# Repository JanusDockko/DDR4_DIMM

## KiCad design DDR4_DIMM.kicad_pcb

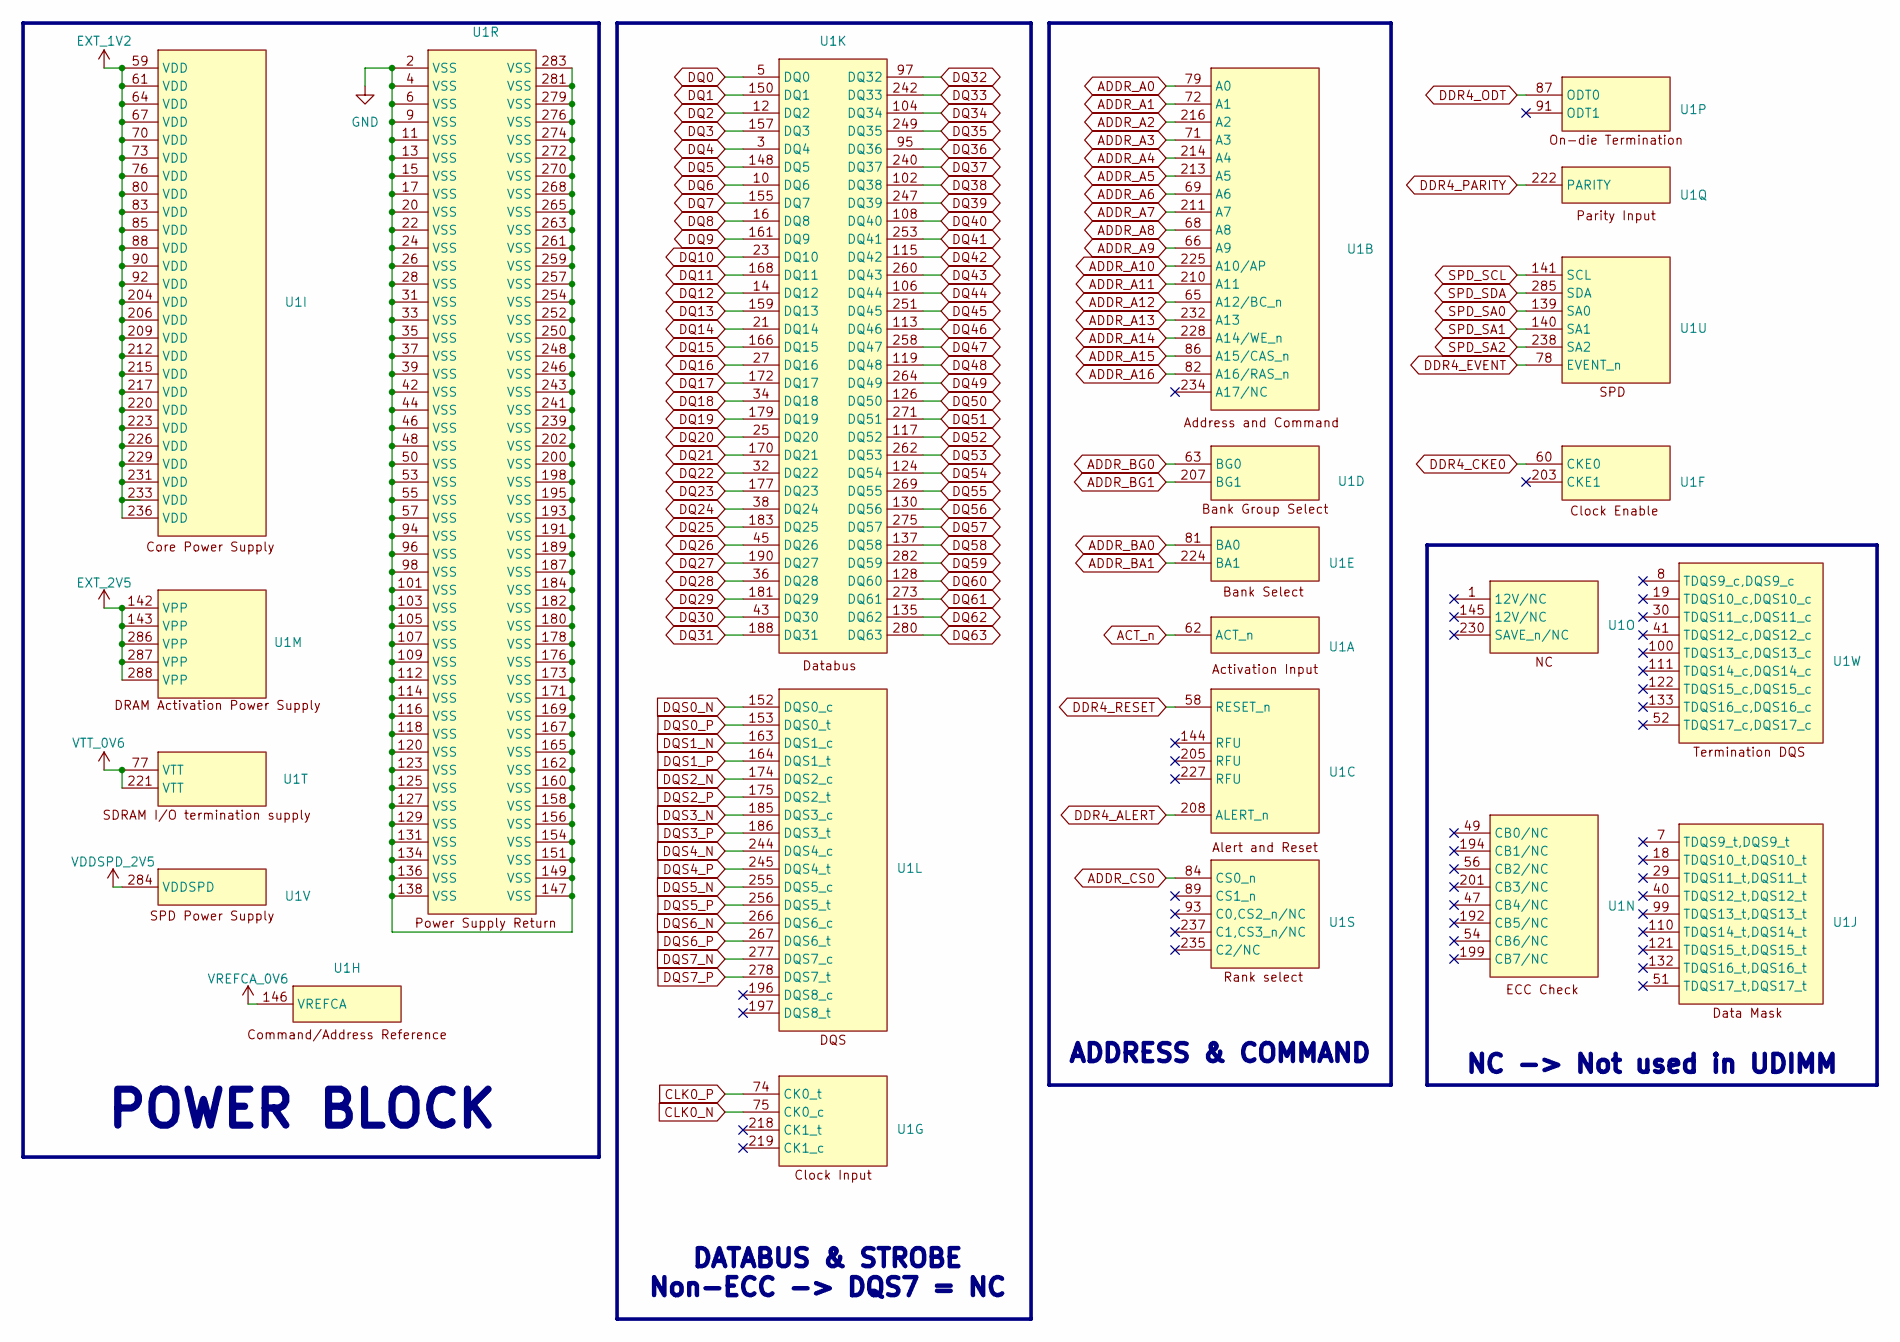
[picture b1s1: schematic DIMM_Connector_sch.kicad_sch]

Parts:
U1: DIMM_Connector_288Pin

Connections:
ACT_n: U1.62 (ACT_n); also elsewhere on the board
ADDR_A0: U1.79 (A0); also elsewhere on the board
ADDR_A1: U1.72 (A1); also elsewhere on the board
ADDR_A2: U1.216 (A2); also elsewhere on the board
ADDR_A3: U1.71 (A3); also elsewhere on the board
ADDR_A4: U1.214 (A4); also elsewhere on the board
ADDR_A5: U1.213 (A5); also elsewhere on the board
ADDR_A6: U1.69 (A6); also elsewhere on the board
ADDR_A7: U1.211 (A7); also elsewhere on the board
ADDR_A8: U1.68 (A8); also elsewhere on the board
ADDR_A9: U1.66 (A9); also elsewhere on the board
ADDR_A10: U1.225 (A10/AP); also elsewhere on the board
ADDR_A11: U1.210 (A11); also elsewhere on the board
ADDR_A12: U1.65 (A12/BC_n); also elsewhere on the board
ADDR_A13: U1.232 (A13); also elsewhere on the board
ADDR_A14: U1.228 (A14/WE_n); also elsewhere on the board
ADDR_A15: U1.86 (A15/CAS_n); also elsewhere on the board
ADDR_A16: U1.82 (A16/RAS_n); also elsewhere on the board
ADDR_BA0: U1.81 (BA0); also elsewhere on the board
ADDR_BA1: U1.224 (BA1); also elsewhere on the board
ADDR_BG0: U1.63 (BG0); also elsewhere on the board
ADDR_BG1: U1.207 (BG1); also elsewhere on the board
ADDR_CS0: U1.84 (CS0_n); also elsewhere on the board
CLK0_N: U1.75 (CK0_c); also elsewhere on the board
CLK0_P: U1.74 (CK0_t); also elsewhere on the board
DDR4_ALERT: U1.208 (ALERT_n); also elsewhere on the board
DDR4_CKE0: U1.60 (CKE0); also elsewhere on the board
DDR4_EVENT: U1.78 (EVENT_n); also elsewhere on the board
DDR4_ODT: U1.87 (ODT0); also elsewhere on the board
DDR4_PARITY: U1.222 (PARITY); also elsewhere on the board
DDR4_RESET: U1.58 (RESET_n); also elsewhere on the board
DQ0: U1.5 (DQ0); also elsewhere on the board
DQ1: U1.150 (DQ1); also elsewhere on the board
DQ2: U1.12 (DQ2); also elsewhere on the board
DQ3: U1.157 (DQ3); also elsewhere on the board
DQ4: U1.3 (DQ4); also elsewhere on the board
DQ5: U1.148 (DQ5); also elsewhere on the board
DQ6: U1.10 (DQ6); also elsewhere on the board
DQ7: U1.155 (DQ7); also elsewhere on the board
DQ8: U1.16 (DQ8); also elsewhere on the board
DQ9: U1.161 (DQ9); also elsewhere on the board
DQ10: U1.23 (DQ10); also elsewhere on the board
DQ11: U1.168 (DQ11); also elsewhere on the board
DQ12: U1.14 (DQ12); also elsewhere on the board
DQ13: U1.159 (DQ13); also elsewhere on the board
DQ14: U1.21 (DQ14); also elsewhere on the board
DQ15: U1.166 (DQ15); also elsewhere on the board
DQ16: U1.27 (DQ16); also elsewhere on the board
DQ17: U1.172 (DQ17); also elsewhere on the board
DQ18: U1.34 (DQ18); also elsewhere on the board
DQ19: U1.179 (DQ19); also elsewhere on the board
DQ20: U1.25 (DQ20); also elsewhere on the board
DQ21: U1.170 (DQ21); also elsewhere on the board
DQ22: U1.32 (DQ22); also elsewhere on the board
DQ23: U1.177 (DQ23); also elsewhere on the board
DQ24: U1.38 (DQ24); also elsewhere on the board
DQ25: U1.183 (DQ25); also elsewhere on the board
DQ26: U1.45 (DQ26); also elsewhere on the board
DQ27: U1.190 (DQ27); also elsewhere on the board
DQ28: U1.36 (DQ28); also elsewhere on the board
DQ29: U1.181 (DQ29); also elsewhere on the board
DQ30: U1.43 (DQ30); also elsewhere on the board
DQ31: U1.188 (DQ31); also elsewhere on the board
DQ32: U1.97 (DQ32); also elsewhere on the board
DQ33: U1.242 (DQ33); also elsewhere on the board
DQ34: U1.104 (DQ34); also elsewhere on the board
DQ35: U1.249 (DQ35); also elsewhere on the board
DQ36: U1.95 (DQ36); also elsewhere on the board
DQ37: U1.240 (DQ37); also elsewhere on the board
DQ38: U1.102 (DQ38); also elsewhere on the board
DQ39: U1.247 (DQ39); also elsewhere on the board
DQ40: U1.108 (DQ40); also elsewhere on the board
DQ41: U1.253 (DQ41); also elsewhere on the board
DQ42: U1.115 (DQ42); also elsewhere on the board
DQ43: U1.260 (DQ43); also elsewhere on the board
DQ44: U1.106 (DQ44); also elsewhere on the board
DQ45: U1.251 (DQ45); also elsewhere on the board
DQ46: U1.113 (DQ46); also elsewhere on the board
DQ47: U1.258 (DQ47); also elsewhere on the board
DQ48: U1.119 (DQ48); also elsewhere on the board
DQ49: U1.264 (DQ49); also elsewhere on the board
DQ50: U1.126 (DQ50); also elsewhere on the board
DQ51: U1.271 (DQ51); also elsewhere on the board
DQ52: U1.117 (DQ52); also elsewhere on the board
DQ53: U1.262 (DQ53); also elsewhere on the board
DQ54: U1.124 (DQ54); also elsewhere on the board
DQ55: U1.269 (DQ55); also elsewhere on the board
DQ56: U1.130 (DQ56); also elsewhere on the board
DQ57: U1.275 (DQ57); also elsewhere on the board
DQ58: U1.137 (DQ58); also elsewhere on the board
DQ59: U1.282 (DQ59); also elsewhere on the board
DQ60: U1.128 (DQ60); also elsewhere on the board
DQ61: U1.273 (DQ61); also elsewhere on the board
DQ62: U1.135 (DQ62); also elsewhere on the board
DQ63: U1.280 (DQ63); also elsewhere on the board
DQS0_N: U1.152 (DQS0_c); also elsewhere on the board
DQS0_P: U1.153 (DQS0_t); also elsewhere on the board
DQS1_N: U1.163 (DQS1_c); also elsewhere on the board
DQS1_P: U1.164 (DQS1_t); also elsewhere on the board
DQS2_N: U1.174 (DQS2_c); also elsewhere on the board
DQS2_P: U1.175 (DQS2_t); also elsewhere on the board
DQS3_N: U1.185 (DQS3_c); also elsewhere on the board
DQS3_P: U1.186 (DQS3_t); also elsewhere on the board
DQS4_N: U1.244 (DQS4_c); also elsewhere on the board
DQS4_P: U1.245 (DQS4_t); also elsewhere on the board
DQS5_N: U1.255 (DQS5_c); also elsewhere on the board
DQS5_P: U1.256 (DQS5_t); also elsewhere on the board
DQS6_N: U1.266 (DQS6_c); also elsewhere on the board
DQS6_P: U1.267 (DQS6_t); also elsewhere on the board
DQS7_N: U1.277 (DQS7_c); also elsewhere on the board
DQS7_P: U1.278 (DQS7_t); also elsewhere on the board
EXT_1V2: U1.59 (VDD), U1.61 (VDD), U1.64 (VDD), U1.67 (VDD), U1.70 (VDD), U1.73 (VDD), U1.76 (VDD), U1.80 (VDD), U1.83 (VDD), U1.85 (VDD), U1.88 (VDD), U1.90 (VDD), U1.92 (VDD), U1.204 (VDD), U1.206 (VDD), U1.209 (VDD), U1.212 (VDD), U1.215 (VDD), U1.217 (VDD), U1.220 (VDD), U1.223 (VDD), U1.226 (VDD), U1.229 (VDD), U1.231 (VDD), U1.233 (VDD), U1.236 (VDD); also elsewhere on the board
EXT_2V5: U1.142 (VPP), U1.143 (VPP), U1.286 (VPP), U1.287 (VPP), U1.288 (VPP); also elsewhere on the board
GND: U1.2 (VSS), U1.4 (VSS), U1.6 (VSS), U1.9 (VSS), U1.11 (VSS), U1.13 (VSS), U1.15 (VSS), U1.17 (VSS), U1.20 (VSS), U1.22 (VSS), U1.24 (VSS), U1.26 (VSS), U1.28 (VSS), U1.31 (VSS), U1.33 (VSS), U1.35 (VSS), U1.37 (VSS), U1.39 (VSS), U1.42 (VSS), U1.44 (VSS), U1.46 (VSS), U1.48 (VSS), U1.50 (VSS), U1.53 (VSS), U1.55 (VSS), U1.57 (VSS), U1.94 (VSS), U1.96 (VSS), U1.98 (VSS), U1.101 (VSS), U1.103 (VSS), U1.105 (VSS), U1.107 (VSS), U1.109 (VSS), U1.112 (VSS), U1.114 (VSS), U1.116 (VSS), U1.118 (VSS), U1.120 (VSS), U1.123 (VSS), U1.125 (VSS), U1.127 (VSS), U1.129 (VSS), U1.131 (VSS), U1.134 (VSS), U1.136 (VSS), U1.138 (VSS), U1.147 (VSS), U1.149 (VSS), U1.151 (VSS), U1.154 (VSS), U1.156 (VSS), U1.158 (VSS), U1.160 (VSS), U1.162 (VSS), U1.165 (VSS), U1.167 (VSS), U1.169 (VSS), U1.171 (VSS), U1.173 (VSS), U1.176 (VSS), U1.178 (VSS), U1.180 (VSS), U1.182 (VSS), U1.184 (VSS), U1.187 (VSS), U1.189 (VSS), U1.191 (VSS), U1.193 (VSS), U1.195 (VSS), U1.198 (VSS), U1.200 (VSS), U1.202 (VSS), U1.239 (VSS), U1.241 (VSS), U1.243 (VSS), U1.246 (VSS), U1.248 (VSS), U1.250 (VSS), U1.252 (VSS), U1.254 (VSS), U1.257 (VSS), U1.259 (VSS), U1.261 (VSS), U1.263 (VSS), U1.265 (VSS), U1.268 (VSS), U1.270 (VSS), U1.272 (VSS), U1.274 (VSS), U1.276 (VSS), U1.279 (VSS), U1.281 (VSS), U1.283 (VSS); also elsewhere on the board
SPD_SA0: U1.139 (SA0); also elsewhere on the board
SPD_SA1: U1.140 (SA1); also elsewhere on the board
SPD_SA2: U1.238 (SA2); also elsewhere on the board
SPD_SCL: U1.141 (SCL); also elsewhere on the board
SPD_SDA: U1.285 (SDA); also elsewhere on the board
VDDSPD_2V5: U1.284 (VDDSPD); also elsewhere on the board
VREFCA_0V6: U1.146 (VREFCA); also elsewhere on the board
VTT_0V6: U1.77 (VTT), U1.221 (VTT); also elsewhere on the board

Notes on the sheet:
NC -> Not used in UDIMM
ADDRESS & COMMAND
DATABUS & STROBE Non-ECC -> DQS7 = NC
POWER BLOCK

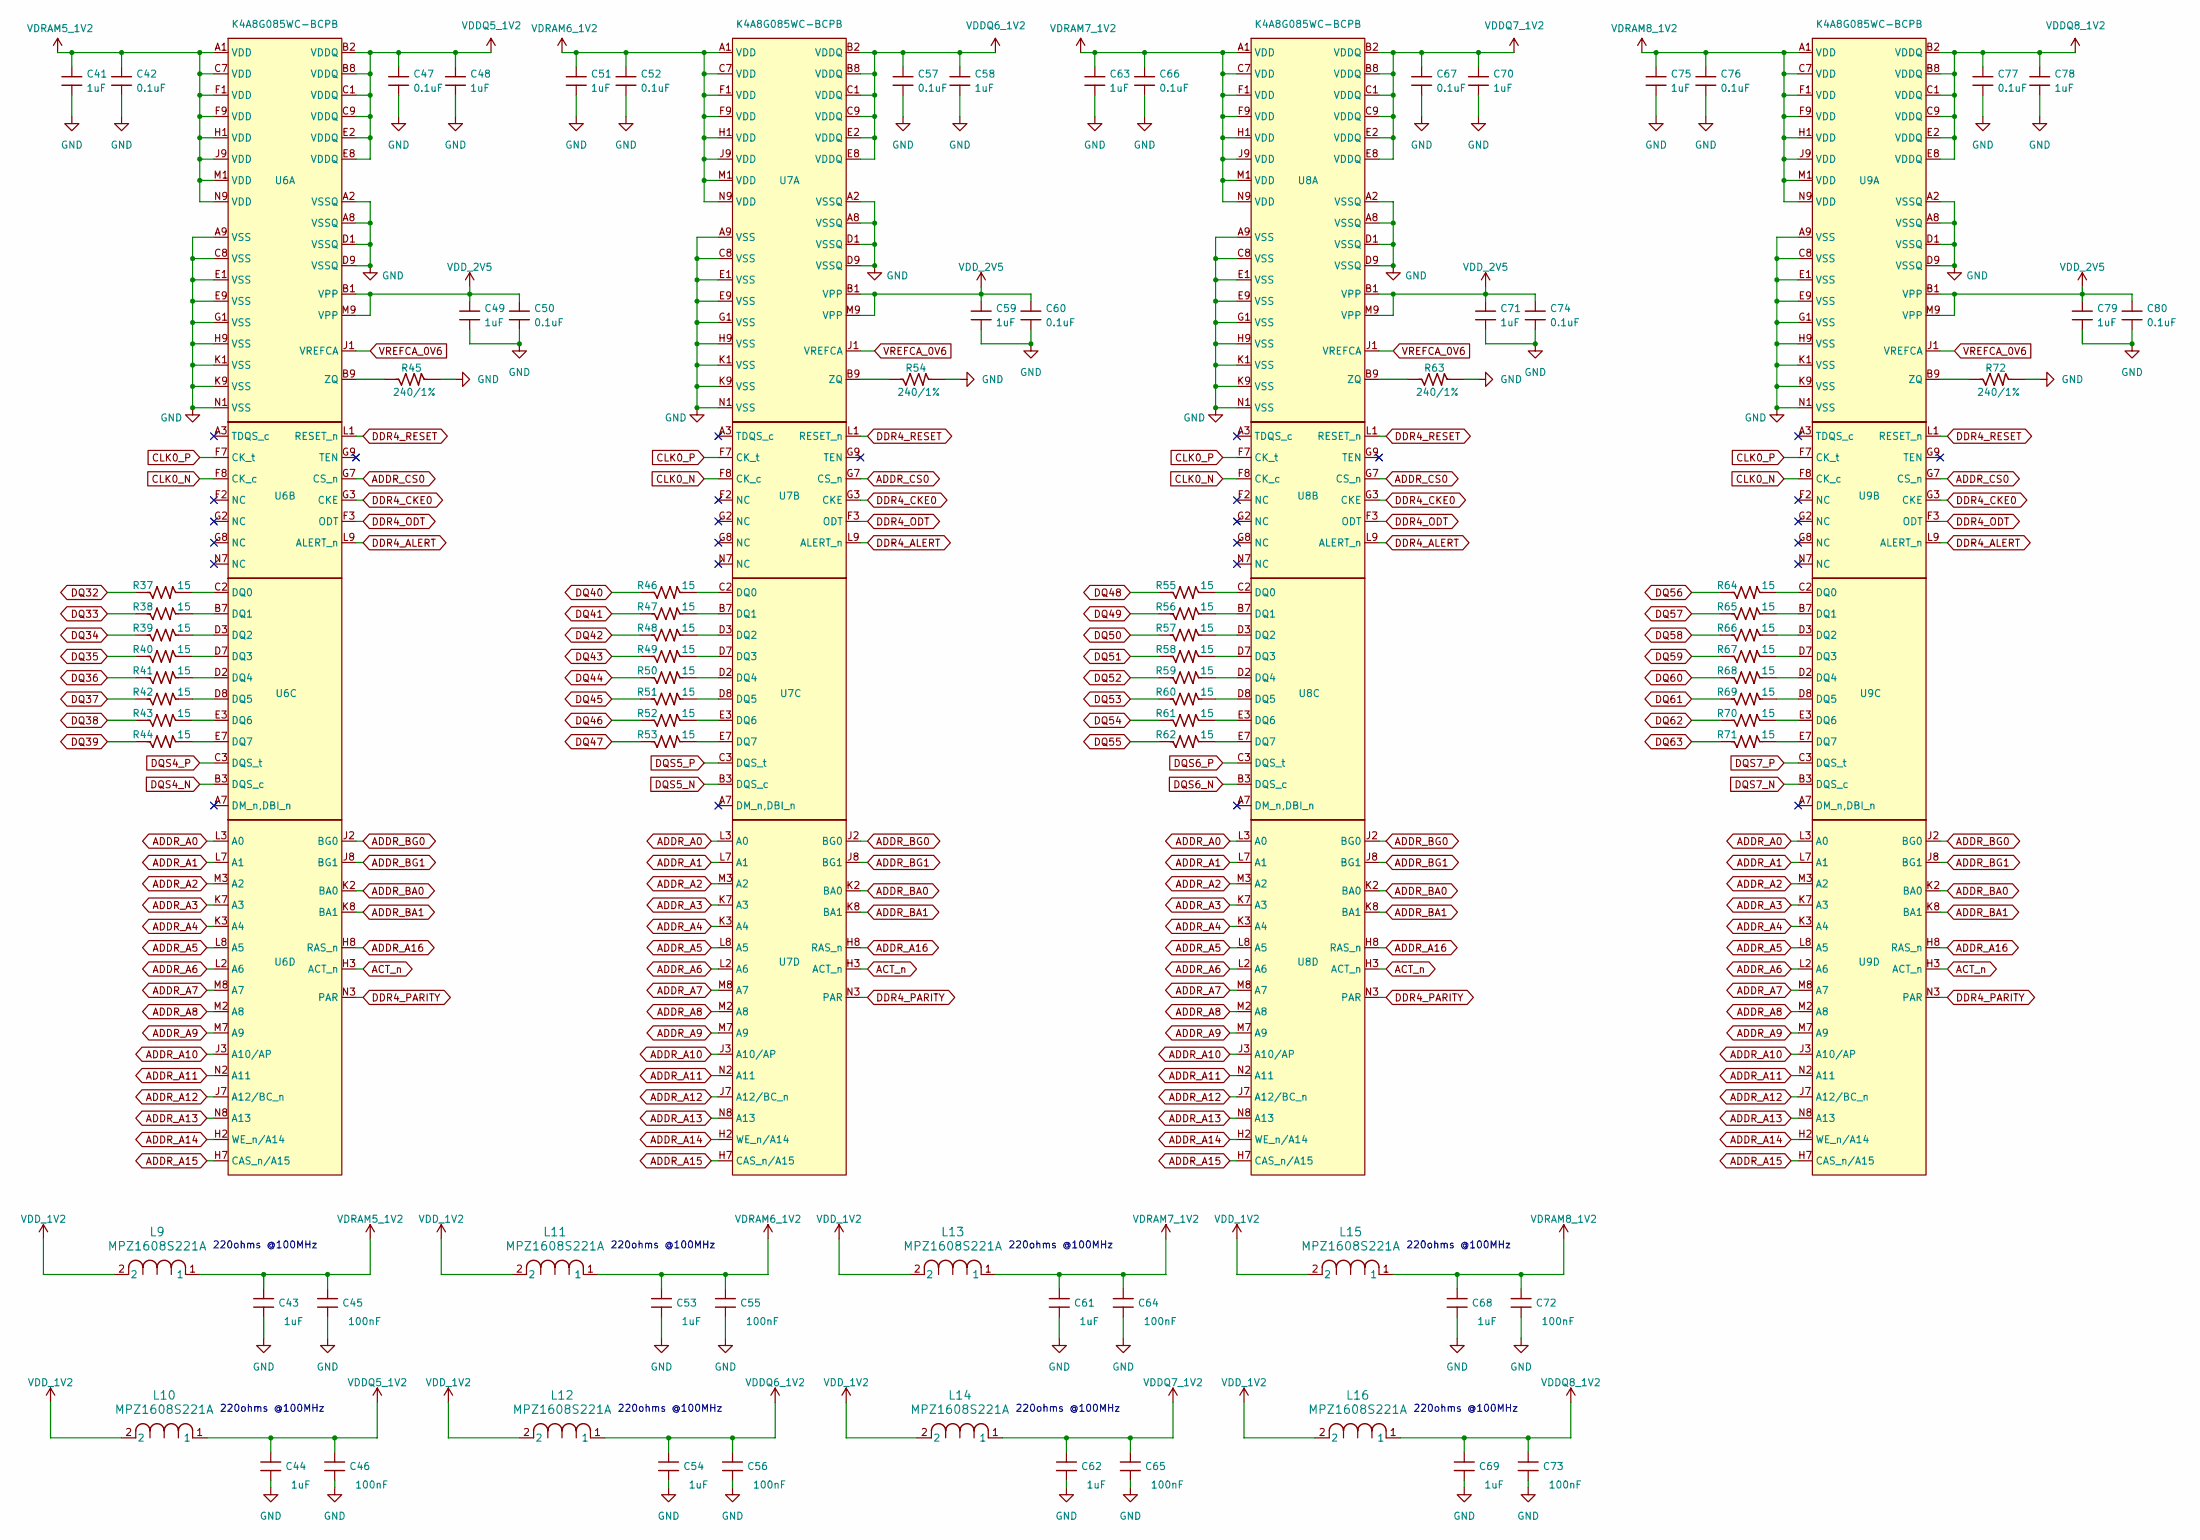
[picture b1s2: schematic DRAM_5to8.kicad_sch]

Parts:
C41, C43, C44, C48, C49, C51, C53, C54, C58, C59, C61, C62, C63, C68, C69, C70, C71, C75, C78, C79: 1uF; C_0402_1005
C42, C47, C50, C52, C57, C60, C66, C67, C74, C76, C77, C80: 0.1uF; C_0402_1005
C45, C46, C55, C56, C64, C65, C72, C73: 100nF; C_0402_1005
L9, L10, L11, L12, L13, L14, L15, L16: MPZ1608S221A; MPZ1608S260ATAH0
R37, R38, R39, R40, R41, R42, R43, R44, R46, R47, R48, R49, R50, R51, R52, R53, R55, R56, R57, R58, R59, R60, R61, R62, R64, R65, R66, R67, R68, R69, R70, R71: 15; R_0402_1005
R45, R54, R63, R72: 240/1%; R_0402_1005
U6, U7, U8, U9: K4A8G085WC-BCPB

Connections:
ACT_n: U6.H3 (ACT_n), U7.H3 (ACT_n), U8.H3 (ACT_n), U9.H3 (ACT_n); also elsewhere on the board
ADDR_A0: U6.L3 (A0), U7.L3 (A0), U8.L3 (A0), U9.L3 (A0); also elsewhere on the board
ADDR_A1: U6.L7 (A1), U7.L7 (A1), U8.L7 (A1), U9.L7 (A1); also elsewhere on the board
ADDR_A2: U6.M3 (A2), U7.M3 (A2), U8.M3 (A2), U9.M3 (A2); also elsewhere on the board
ADDR_A3: U6.K7 (A3), U7.K7 (A3), U8.K7 (A3), U9.K7 (A3); also elsewhere on the board
ADDR_A4: U6.K3 (A4), U7.K3 (A4), U8.K3 (A4), U9.K3 (A4); also elsewhere on the board
ADDR_A5: U6.L8 (A5), U7.L8 (A5), U8.L8 (A5), U9.L8 (A5); also elsewhere on the board
ADDR_A6: U6.L2 (A6), U7.L2 (A6), U8.L2 (A6), U9.L2 (A6); also elsewhere on the board
ADDR_A7: U6.M8 (A7), U7.M8 (A7), U8.M8 (A7), U9.M8 (A7); also elsewhere on the board
ADDR_A8: U6.M2 (A8), U7.M2 (A8), U8.M2 (A8), U9.M2 (A8); also elsewhere on the board
ADDR_A9: U6.M7 (A9), U7.M7 (A9), U8.M7 (A9), U9.M7 (A9); also elsewhere on the board
ADDR_A10: U6.J3 (A10/AP), U7.J3 (A10/AP), U8.J3 (A10/AP), U9.J3 (A10/AP); also elsewhere on the board
ADDR_A11: U6.N2 (A11), U7.N2 (A11), U8.N2 (A11), U9.N2 (A11); also elsewhere on the board
ADDR_A12: U6.J7 (A12/BC_n), U7.J7 (A12/BC_n), U8.J7 (A12/BC_n), U9.J7 (A12/BC_n); also elsewhere on the board
ADDR_A13: U6.N8 (A13), U7.N8 (A13), U8.N8 (A13), U9.N8 (A13); also elsewhere on the board
ADDR_A14: U6.H2 (WE_n/A14), U7.H2 (WE_n/A14), U8.H2 (WE_n/A14), U9.H2 (WE_n/A14); also elsewhere on the board
ADDR_A15: U6.H7 (CAS_n/A15), U7.H7 (CAS_n/A15), U8.H7 (CAS_n/A15), U9.H7 (CAS_n/A15); also elsewhere on the board
ADDR_A16: U6.H8 (RAS_n), U7.H8 (RAS_n), U8.H8 (RAS_n), U9.H8 (RAS_n); also elsewhere on the board
ADDR_BA0: U6.K2 (BA0), U7.K2 (BA0), U8.K2 (BA0), U9.K2 (BA0); also elsewhere on the board
ADDR_BA1: U6.K8 (BA1), U7.K8 (BA1), U8.K8 (BA1), U9.K8 (BA1); also elsewhere on the board
ADDR_BG0: U6.J2 (BG0), U7.J2 (BG0), U8.J2 (BG0), U9.J2 (BG0); also elsewhere on the board
ADDR_BG1: U6.J8 (BG1), U7.J8 (BG1), U8.J8 (BG1), U9.J8 (BG1); also elsewhere on the board
ADDR_CS0: U6.G7 (CS_n), U7.G7 (CS_n), U8.G7 (CS_n), U9.G7 (CS_n); also elsewhere on the board
CLK0_N: U6.F8 (CK_c), U7.F8 (CK_c), U8.F8 (CK_c), U9.F8 (CK_c); also elsewhere on the board
CLK0_P: U6.F7 (CK_t), U7.F7 (CK_t), U8.F7 (CK_t), U9.F7 (CK_t); also elsewhere on the board
DDR4_ALERT: U6.L9 (ALERT_n), U7.L9 (ALERT_n), U8.L9 (ALERT_n), U9.L9 (ALERT_n); also elsewhere on the board
DDR4_CKE0: U6.G3 (CKE), U7.G3 (CKE), U8.G3 (CKE), U9.G3 (CKE); also elsewhere on the board
DDR4_ODT: U6.F3 (ODT), U7.F3 (ODT), U8.F3 (ODT), U9.F3 (ODT); also elsewhere on the board
DDR4_PARITY: U6.N3 (PAR), U7.N3 (PAR), U8.N3 (PAR), U9.N3 (PAR); also elsewhere on the board
DDR4_RESET: U6.L1 (RESET_n), U7.L1 (RESET_n), U8.L1 (RESET_n), U9.L1 (RESET_n); also elsewhere on the board
DQ32: R37.1; also elsewhere on the board
DQ33: R38.1; also elsewhere on the board
DQ34: R39.1; also elsewhere on the board
DQ35: R40.1; also elsewhere on the board
DQ36: R41.1; also elsewhere on the board
DQ37: R42.1; also elsewhere on the board
DQ38: R43.1; also elsewhere on the board
DQ39: R44.1; also elsewhere on the board
DQ40: R46.1; also elsewhere on the board
DQ41: R47.1; also elsewhere on the board
DQ42: R48.1; also elsewhere on the board
DQ43: R49.1; also elsewhere on the board
DQ44: R50.1; also elsewhere on the board
DQ45: R51.1; also elsewhere on the board
DQ46: R52.1; also elsewhere on the board
DQ47: R53.1; also elsewhere on the board
DQ48: R55.1; also elsewhere on the board
DQ49: R56.1; also elsewhere on the board
DQ50: R57.1; also elsewhere on the board
DQ51: R58.1; also elsewhere on the board
DQ52: R59.1; also elsewhere on the board
DQ53: R60.1; also elsewhere on the board
DQ54: R61.1; also elsewhere on the board
DQ55: R62.1; also elsewhere on the board
DQ56: R64.1; also elsewhere on the board
DQ57: R65.1; also elsewhere on the board
DQ58: R66.1; also elsewhere on the board
DQ59: R67.1; also elsewhere on the board
DQ60: R68.1; also elsewhere on the board
DQ61: R69.1; also elsewhere on the board
DQ62: R70.1; also elsewhere on the board
DQ63: R71.1; also elsewhere on the board
DQS4_N: U6.B3 (DQS_c); also elsewhere on the board
DQS4_P: U6.C3 (DQS_t); also elsewhere on the board
DQS5_N: U7.B3 (DQS_c); also elsewhere on the board
DQS5_P: U7.C3 (DQS_t); also elsewhere on the board
DQS6_N: U8.B3 (DQS_c); also elsewhere on the board
DQS6_P: U8.C3 (DQS_t); also elsewhere on the board
DQS7_N: U9.B3 (DQS_c); also elsewhere on the board
DQS7_P: U9.C3 (DQS_t); also elsewhere on the board
GND: C41.1, C42.1, C43.1, C44.1, C45.1, C46.1, C47.1, C48.1, C49.1, C50.1, C51.1, C52.1, C53.1, C54.1, C55.1, C56.1, C57.1, C58.1, C59.1, C60.1, C61.1, C62.1, C63.1, C64.1, C65.1, C66.1, C67.1, C68.1, C69.1, C70.1, C71.1, C72.1, C73.1, C74.1, C75.1, C76.1, C77.1, C78.1, C79.1, C80.1, R45.2, R54.2, R63.2, R72.2, U6.A2 (VSSQ), U6.A8 (VSSQ), U6.A9 (VSS), U6.C8 (VSS), U6.D1 (VSSQ), U6.D9 (VSSQ), U6.E1 (VSS), U6.E9 (VSS), U6.G1 (VSS), U6.H9 (VSS), U6.K1 (VSS), U6.K9 (VSS), U6.N1 (VSS), U7.A2 (VSSQ), U7.A8 (VSSQ), U7.A9 (VSS), U7.C8 (VSS), U7.D1 (VSSQ), U7.D9 (VSSQ), U7.E1 (VSS), U7.E9 (VSS), U7.G1 (VSS), U7.H9 (VSS), U7.K1 (VSS), U7.K9 (VSS), U7.N1 (VSS), U8.A2 (VSSQ), U8.A8 (VSSQ), U8.A9 (VSS), U8.C8 (VSS), U8.D1 (VSSQ), U8.D9 (VSSQ), U8.E1 (VSS), U8.E9 (VSS), U8.G1 (VSS), U8.H9 (VSS), U8.K1 (VSS), U8.K9 (VSS), U8.N1 (VSS), U9.A2 (VSSQ), U9.A8 (VSSQ), U9.A9 (VSS), U9.C8 (VSS), U9.D1 (VSSQ), U9.D9 (VSSQ), U9.E1 (VSS), U9.E9 (VSS), U9.G1 (VSS), U9.H9 (VSS), U9.K1 (VSS), U9.K9 (VSS), U9.N1 (VSS); also elsewhere on the board
unnamed: R45.1, U6.B9 (ZQ)
unnamed: R37.2, U6.C2 (DQ0)
unnamed: R38.2, U6.B7 (DQ1)
unnamed: R39.2, U6.D3 (DQ2)
unnamed: R40.2, U6.D7 (DQ3)
unnamed: R41.2, U6.D2 (DQ4)
unnamed: R42.2, U6.D8 (DQ5)
unnamed: R43.2, U6.E3 (DQ6)
unnamed: R44.2, U6.E7 (DQ7)
unnamed: R54.1, U7.B9 (ZQ)
unnamed: R46.2, U7.C2 (DQ0)
unnamed: R47.2, U7.B7 (DQ1)
unnamed: R48.2, U7.D3 (DQ2)
unnamed: R49.2, U7.D7 (DQ3)
unnamed: R50.2, U7.D2 (DQ4)
unnamed: R51.2, U7.D8 (DQ5)
unnamed: R52.2, U7.E3 (DQ6)
unnamed: R53.2, U7.E7 (DQ7)
unnamed: R63.1, U8.B9 (ZQ)
unnamed: R55.2, U8.C2 (DQ0)
unnamed: R56.2, U8.B7 (DQ1)
unnamed: R57.2, U8.D3 (DQ2)
unnamed: R58.2, U8.D7 (DQ3)
unnamed: R59.2, U8.D2 (DQ4)
unnamed: R60.2, U8.D8 (DQ5)
unnamed: R61.2, U8.E3 (DQ6)
unnamed: R62.2, U8.E7 (DQ7)
unnamed: R72.1, U9.B9 (ZQ)
unnamed: R64.2, U9.C2 (DQ0)
unnamed: R65.2, U9.B7 (DQ1)
unnamed: R66.2, U9.D3 (DQ2)
unnamed: R67.2, U9.D7 (DQ3)
unnamed: R68.2, U9.D2 (DQ4)
unnamed: R69.2, U9.D8 (DQ5)
unnamed: R70.2, U9.E3 (DQ6)
unnamed: R71.2, U9.E7 (DQ7)
VDDQ5_1V2: C44.2, C46.2, C47.2, C48.2, L10.1, U6.B2 (VDDQ), U6.B8 (VDDQ), U6.C1 (VDDQ), U6.C9 (VDDQ), U6.E2 (VDDQ), U6.E8 (VDDQ)
VDDQ6_1V2: C54.2, C56.2, C57.2, C58.2, L12.1, U7.B2 (VDDQ), U7.B8 (VDDQ), U7.C1 (VDDQ), U7.C9 (VDDQ), U7.E2 (VDDQ), U7.E8 (VDDQ)
VDDQ7_1V2: C62.2, C65.2, C67.2, C70.2, L14.1, U8.B2 (VDDQ), U8.B8 (VDDQ), U8.C1 (VDDQ), U8.C9 (VDDQ), U8.E2 (VDDQ), U8.E8 (VDDQ)
VDDQ8_1V2: C69.2, C73.2, C77.2, C78.2, L16.1, U9.B2 (VDDQ), U9.B8 (VDDQ), U9.C1 (VDDQ), U9.C9 (VDDQ), U9.E2 (VDDQ), U9.E8 (VDDQ)
VDD_1V2: L9.2, L10.2, L11.2, L12.2, L13.2, L14.2, L15.2, L16.2; also elsewhere on the board
VDD_2V5: C49.2, C50.2, C59.2, C60.2, C71.2, C74.2, C79.2, C80.2, U6.B1 (VPP), U6.M9 (VPP), U7.B1 (VPP), U7.M9 (VPP), U8.B1 (VPP), U8.M9 (VPP), U9.B1 (VPP), U9.M9 (VPP); also elsewhere on the board
VDRAM5_1V2: C41.2, C42.2, C43.2, C45.2, L9.1, U6.A1 (VDD), U6.C7 (VDD), U6.F1 (VDD), U6.F9 (VDD), U6.H1 (VDD), U6.J9 (VDD), U6.M1 (VDD), U6.N9 (VDD)
VDRAM6_1V2: C51.2, C52.2, C53.2, C55.2, L11.1, U7.A1 (VDD), U7.C7 (VDD), U7.F1 (VDD), U7.F9 (VDD), U7.H1 (VDD), U7.J9 (VDD), U7.M1 (VDD), U7.N9 (VDD)
VDRAM7_1V2: C61.2, C63.2, C64.2, C66.2, L13.1, U8.A1 (VDD), U8.C7 (VDD), U8.F1 (VDD), U8.F9 (VDD), U8.H1 (VDD), U8.J9 (VDD), U8.M1 (VDD), U8.N9 (VDD)
VDRAM8_1V2: C68.2, C72.2, C75.2, C76.2, L15.1, U9.A1 (VDD), U9.C7 (VDD), U9.F1 (VDD), U9.F9 (VDD), U9.H1 (VDD), U9.J9 (VDD), U9.M1 (VDD), U9.N9 (VDD)
VREFCA_0V6: U6.J1 (VREFCA), U7.J1 (VREFCA), U8.J1 (VREFCA), U9.J1 (VREFCA); also elsewhere on the board

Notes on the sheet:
220ohms @100MHz
